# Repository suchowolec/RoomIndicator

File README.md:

# RoomIndicator
Small AVR project designed to indicate the room occupancy based on light.

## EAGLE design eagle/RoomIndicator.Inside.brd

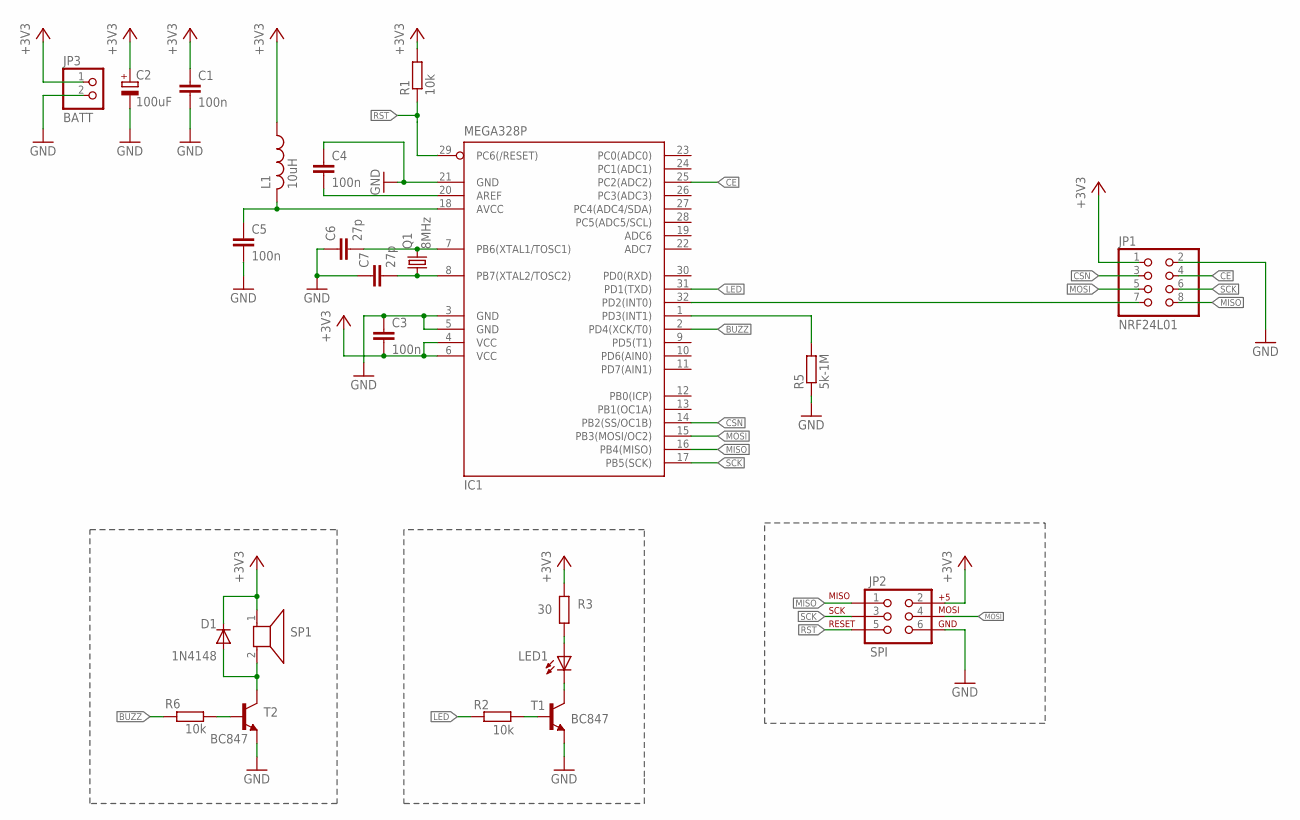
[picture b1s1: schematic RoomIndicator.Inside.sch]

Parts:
C1: 100n; C025-025X050
C2: 100uF; E2,5-5
C3, C4, C5: 100n; C0805K
C6, C7: 27p; C0805K
D1: 1N4148; DO35-7
IC1: MEGA328P; TQFP32-08
JP1: NRF24L01; 2X04
JP2: SPI; 2X3
JP3: BATT; 1X02
L1: 10uH; 0204/7
LED1: GREEN; LED5MM
Q1: 8MHz; HC49/S
R1, R2, R6: 10k; R0805
R3: 30; 0204/5
R5: 5k-1M; 0204/5
SP1: AL60PWIDE; AL80P
T1, T2: BC847; SOT23

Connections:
+3V3: C1.1, C2.+, C3.2, D1.C, IC1.4 (VCC), IC1.6 (VCC), JP1.1, JP2.2, JP3.1, L1.1, R1.2, R3.1, SP1.1
AVCC: C5.1, IC1.18 (AVCC), L1.2
BUZZ: IC1.2 (PD4(XCK/T0)), R6.1
CE: IC1.25 (PC2(ADC2)), JP1.4
CSN: IC1.14 (PB2(SS/OC1B)), JP1.3
GND: C1.2, C2.-, C3.1, C4.1, C5.2, C6.1, C7.1, IC1.3 (GND), IC1.5 (GND), IC1.21 (GND), JP1.2, JP2.6, JP3.2, R5.1, T1.2 (E), T2.2 (E)
INT0: IC1.32 (PD2(INT0)), JP1.7
INT1: IC1.1 (PD3(INT1)), R5.2
LED: IC1.31 (PD1(TXD)), R2.2
MISO: IC1.16 (PB4(MISO)), JP1.8, JP2.1
MOSI: IC1.15 (PB3(MOSI/OC2)), JP1.5, JP2.4
unnamed: C4.2, IC1.20 (AREF)
unnamed: R6.2, T2.1 (B)
unnamed: LED1.A, R3.2
unnamed: R2.1, T1.1 (B)
unnamed: LED1.K (C), T1.3 (C)
unnamed: D1.A, SP1.2, T2.3 (C)
RST: IC1.29 (PC6(/RESET)), JP2.5, R1.1
SCK: IC1.17 (PB5(SCK)), JP1.6, JP2.3
TOSC1: C6.2, IC1.7 (PB6(XTAL1/TOSC1)), Q1.2
TOSC2: C7.2, IC1.8 (PB7(XTAL2/TOSC2)), Q1.1

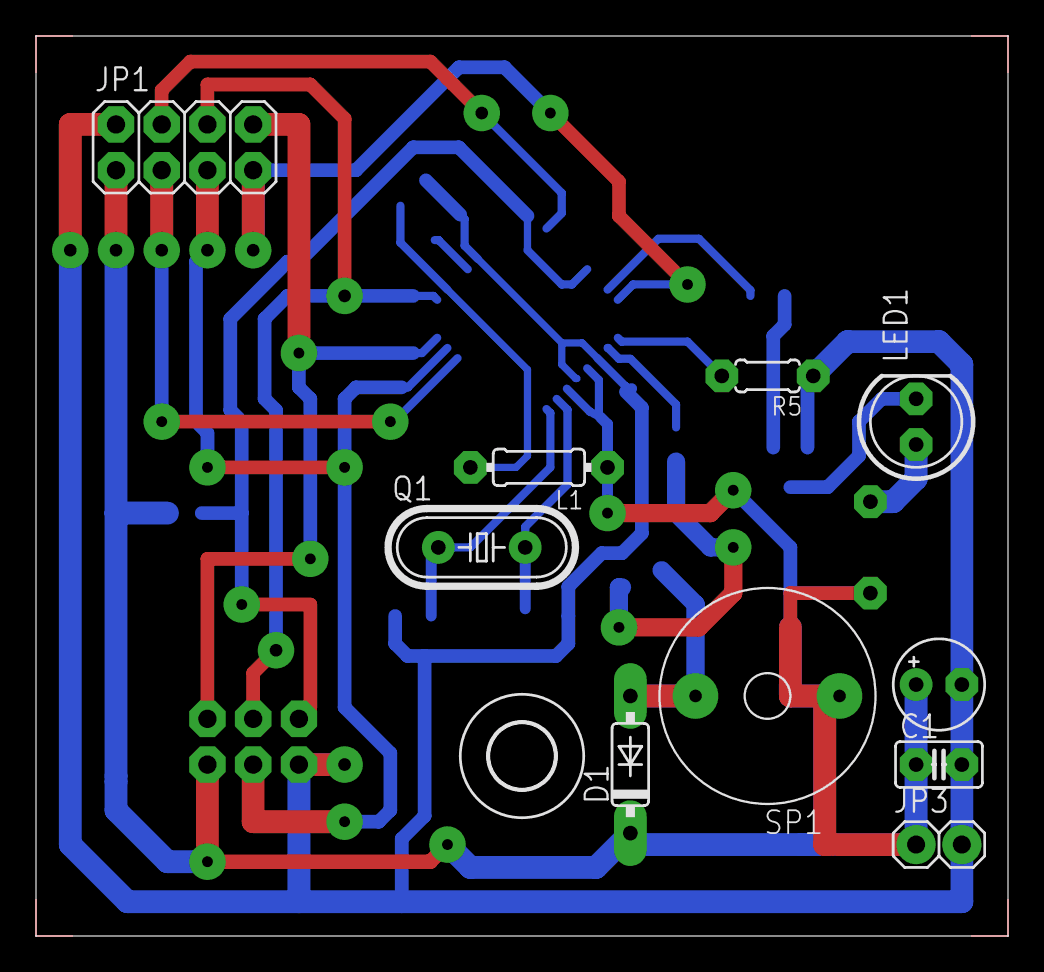
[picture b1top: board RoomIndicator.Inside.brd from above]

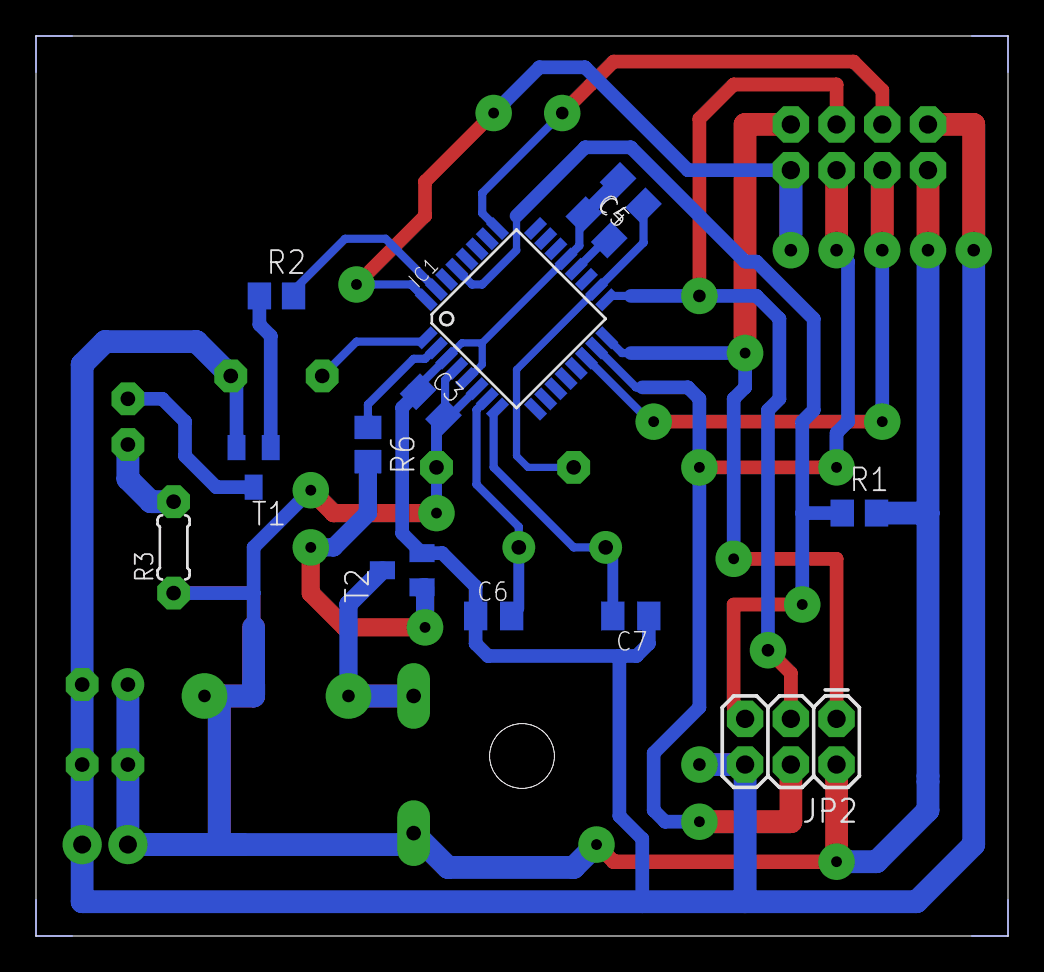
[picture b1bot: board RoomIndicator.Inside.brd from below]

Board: 2 copper layers, 54.0 x 50.0 mm, 24 parts (13 on the bottom side), 21 nets.

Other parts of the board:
U$1: 3,6

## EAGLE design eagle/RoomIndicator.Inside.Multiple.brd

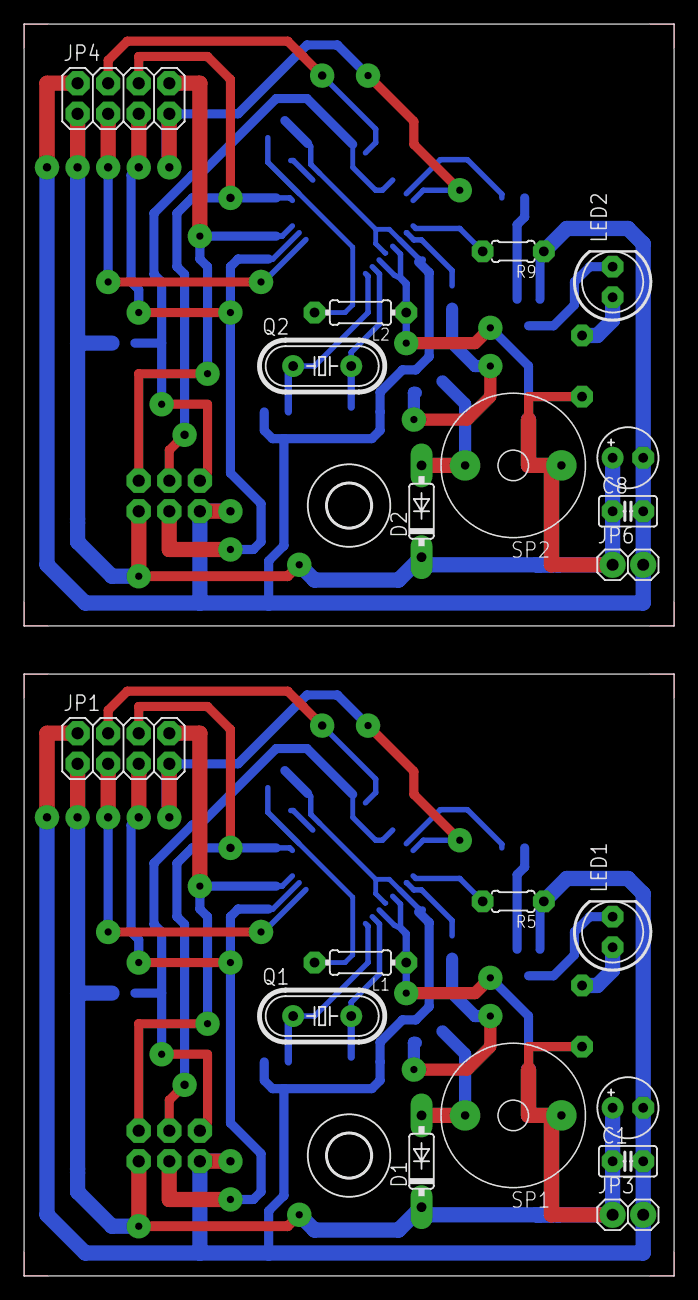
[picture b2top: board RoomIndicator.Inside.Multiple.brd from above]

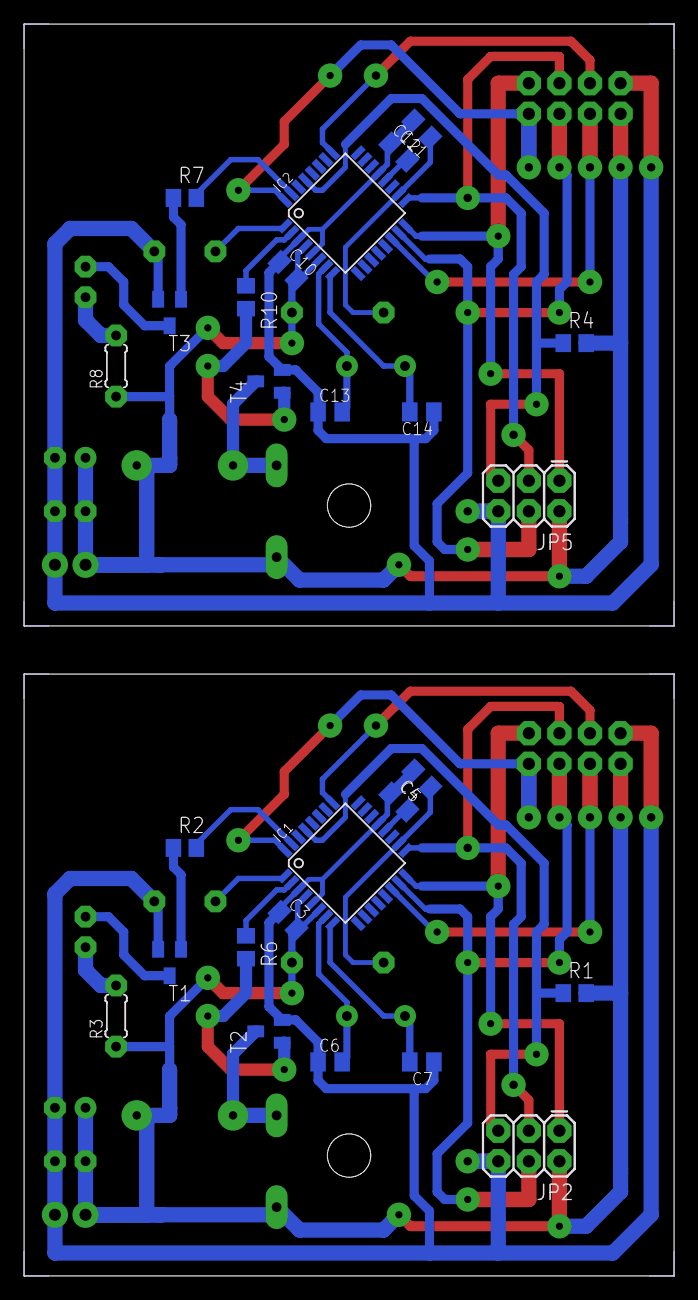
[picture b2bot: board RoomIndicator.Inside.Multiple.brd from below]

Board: 2 copper layers, 54.0 x 104.0 mm, 48 parts (26 on the bottom side), 42 nets.

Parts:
C1, C8: 100n; C025-025X050
C2, C9: 100uF; E2,5-5
C3, C4, C5, C10, C11, C12: 100n; C0805K
C6, C7, C13, C14: 27p; C0805K
D1, D2: 1N4148; DO35-7
IC1, IC2: MEGA328P; TQFP32-08
JP1, JP4: NRF24L01; 2X04
JP2, JP5: SPI; 2X3
JP3, JP6: BATT; 1X02
L1, L2: 10uH; 0204/7
LED1, LED2: GREEN; LED5MM
Q1, Q2: 8MHz; HC49/S
R1, R2, R4, R6, R7, R10: 10k; R0805
R3, R8: 30; 0204/5
R5, R9: 5k-1M; 0204/5
SP1, SP2: AL60PWIDE; AL80P
T1, T2, T3, T4: BC847; SOT23
U$1, U$2: 3,6

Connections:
+3V1: C8.1, C9.+, C10.2, D2.C, IC2.4, IC2.6, JP4.1, JP5.2, JP6.1, L2.1, R4.2, R8.1, SP2.1
+3V3: C1.1, C2.+, C3.2, D1.C, IC1.4, IC1.6, JP1.1, JP2.2, JP3.1, L1.1, R1.2, R3.1, SP1.1
AVCC: C5.1, IC1.18, L1.2
AVCC1: C12.1, IC2.18, L2.2
BUZZ: IC1.2, R6.1
BUZZ1: IC2.2, R10.1
CE: IC1.25, JP1.4
CE1: IC2.25, JP4.4
CSN: IC1.14, JP1.3
CSN1: IC2.14, JP4.3
GND: C1.2, C2.-, C3.1, C4.1, C5.2, C6.1, C7.1, IC1.3, IC1.5, IC1.21, JP1.2, JP2.6, JP3.2, R5.1, T1.2, T2.2
GND1: C8.2, C9.-, C10.1, C11.1, C12.2, C13.1, C14.1, IC2.3, IC2.5, IC2.21, JP4.2, JP5.6, JP6.2, R9.1, T3.2, T4.2
INT0: IC1.32, JP1.7
INT1: IC1.1, R5.2
INT2: IC2.1, R9.2
INT3: IC2.32, JP4.7
LED: IC1.31, R2.2
LED1: IC2.31, R7.2
MISO: IC1.16, JP1.8, JP2.1
MISO1: IC2.16, JP4.8, JP5.1
MOSI: IC1.15, JP1.5, JP2.4
MOSI1: IC2.15, JP4.5, JP5.4
unnamed: C4.2, IC1.20
unnamed: R6.2, T2.1
unnamed: LED1.A, R3.2
unnamed: R2.1, T1.1
unnamed: LED1.K, T1.3
unnamed: C11.2, IC2.20
unnamed: R7.1, T3.1
unnamed: D1.A, SP1.2, T2.3
unnamed: LED2.K, T3.3
unnamed: D2.A, SP2.2, T4.3
unnamed: R10.2, T4.1
unnamed: LED2.A, R8.2
RST: IC1.29, JP2.5, R1.1
RST1: IC2.29, JP5.5, R4.1
SCK: IC1.17, JP1.6, JP2.3
SCK1: IC2.17, JP4.6, JP5.3
TOSC1: C6.2, IC1.7, Q1.2
TOSC2: C7.2, IC1.8, Q1.1
TOSC3: C14.2, IC2.8, Q2.1
TOSC4: C13.2, IC2.7, Q2.2

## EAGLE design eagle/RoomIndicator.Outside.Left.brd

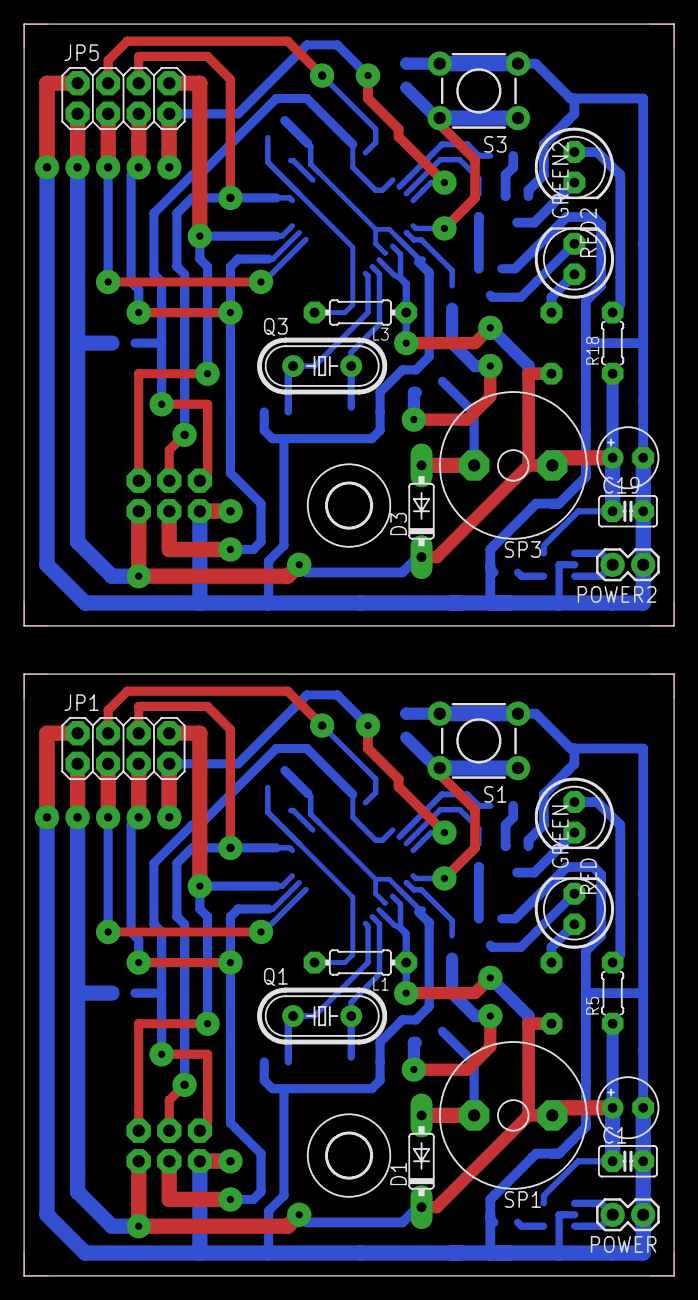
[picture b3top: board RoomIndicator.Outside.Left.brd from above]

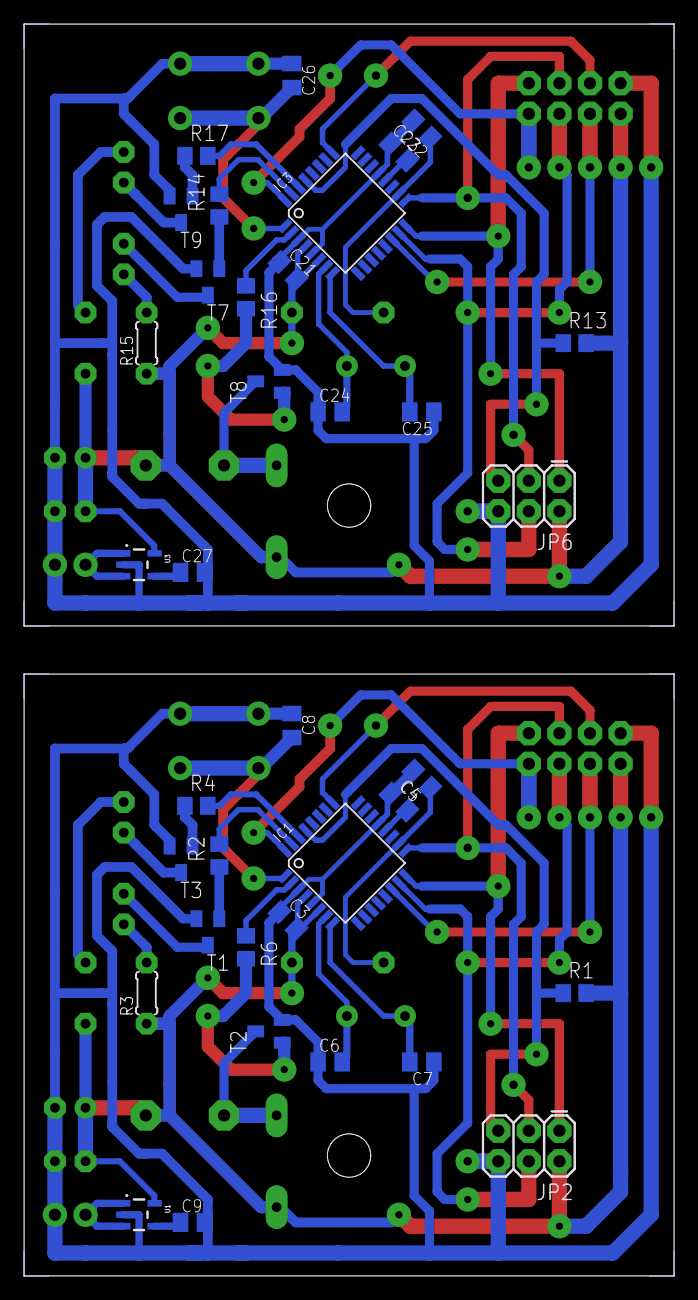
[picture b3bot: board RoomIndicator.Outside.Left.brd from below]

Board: 2 copper layers, 54.0 x 104.0 mm, 62 parts (36 on the bottom side), 54 nets.

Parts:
C1, C19: 100n; C025-025X050
C2, C20: 100uF; E2,5-5
C3, C4, C5, C8, C21, C22, C23, C26: 100n; C0805K
C6, C7, C24, C25: 27p; C0805K
C9, C27: 180p; C0805K
D1, D3: 1N4148; DO35-7
GREEN, GREEN2: GREEN; LED5MM
IC1, IC3: MEGA328P; TQFP32-08
JP1, JP5: NRF24L01; 2X04
JP2, JP6: SPI; 2X3
L1, L3: 10uH; 0204/7
POWER, POWER2: 1X02
Q1, Q3: 8MHz; HC49/S
R1, R2, R4, R6, R13, R14, R16, R17: 10k; R0805
R3, R5, R15, R18: 30; 0204/5
RED, RED2: GREEN; LED5MM
S1, S3: TACTILE-PTH
SP1, SP3: AL60P
T1, T2, T3, T7, T8, T9: BC847; SOT23
U1, U3: 3.3V/150mA; SOT23-5
U$1, U$3: 3,6

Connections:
+3V2: C19.1, C20.+, C21.2, D3.C, IC3.4, IC3.6, JP5.1, JP6.2, L3.1, R13.2, R15.1, R18.1, SP3.1, U3.5
+3V3: C1.1, C2.+, C3.2, D1.C, IC1.4, IC1.6, JP1.1, JP2.2, L1.1, R1.2, R3.1, R5.1, SP1.1, U1.5
AVCC: C5.1, IC1.18, L1.2
AVCC2: C23.1, IC3.18, L3.2
BLUE: IC1.31, R2.2
BLUE2: IC3.31, R14.2
BUZZ: IC1.2, R6.1
BUZZ2: IC3.2, R16.1
CE: IC1.25, JP1.4
CE2: IC3.25, JP5.4
CSN: IC1.14, JP1.3
CSN2: IC3.14, JP5.3
GND: C1.2, C2.-, C3.1, C4.1, C5.2, C6.1, C7.1, C8.1, C9.2, IC1.3, IC1.5, IC1.21, JP1.2, JP2.6, POWER.1, S1.3, S1.4, T1.2, T2.2, T3.2, U1.2
GND2: C19.2, C20.-, C21.1, C22.1, C23.2, C24.1, C25.1, C26.1, C27.2, IC3.3, IC3.5, IC3.21, JP5.2, JP6.6, POWER2.1, S3.3, S3.4, T7.2, T8.2, T9.2, U3.2
INT0: IC1.32, JP1.7
INT1: C8.2, IC1.1, S1.1, S1.2
INT4: C26.2, IC3.1, S3.1, S3.2
INT5: IC3.32, JP5.7
MISO: IC1.16, JP1.8, JP2.1
MISO2: IC3.16, JP5.8, JP6.1
MOSI: IC1.15, JP1.5, JP2.4
MOSI2: IC3.15, JP5.5, JP6.4
unnamed: POWER.2, U1.1, U1.3
unnamed: R4.1, T3.1
unnamed: RED.K, T3.3
unnamed: C4.2, IC1.20
unnamed: R6.2, T2.1
unnamed: GREEN.A, R3.2
unnamed: R5.2, RED.A
unnamed: C9.1, U1.4
unnamed: R2.1, T1.1
unnamed: GREEN.K, T1.3
unnamed: D1.A, SP1.2, T2.3
unnamed: C22.2, IC3.20
unnamed: R14.1, T7.1
unnamed: GREEN2.K, T7.3
unnamed: D3.A, SP3.2, T8.3
unnamed: R16.2, T8.1
unnamed: GREEN2.A, R15.2
unnamed: POWER2.2, U3.1, U3.3
unnamed: R17.1, T9.1
unnamed: RED2.K, T9.3
unnamed: R18.2, RED2.A
unnamed: C27.1, U3.4
RED: IC1.30, R4.2
RED2: IC3.30, R17.2
RST: IC1.29, JP2.5, R1.1
RST2: IC3.29, JP6.5, R13.1
SCK: IC1.17, JP1.6, JP2.3
SCK2: IC3.17, JP5.6, JP6.3
TOSC1: C6.2, IC1.7, Q1.2
TOSC2: C7.2, IC1.8, Q1.1
TOSC5: C25.2, IC3.8, Q3.1
TOSC6: C24.2, IC3.7, Q3.2

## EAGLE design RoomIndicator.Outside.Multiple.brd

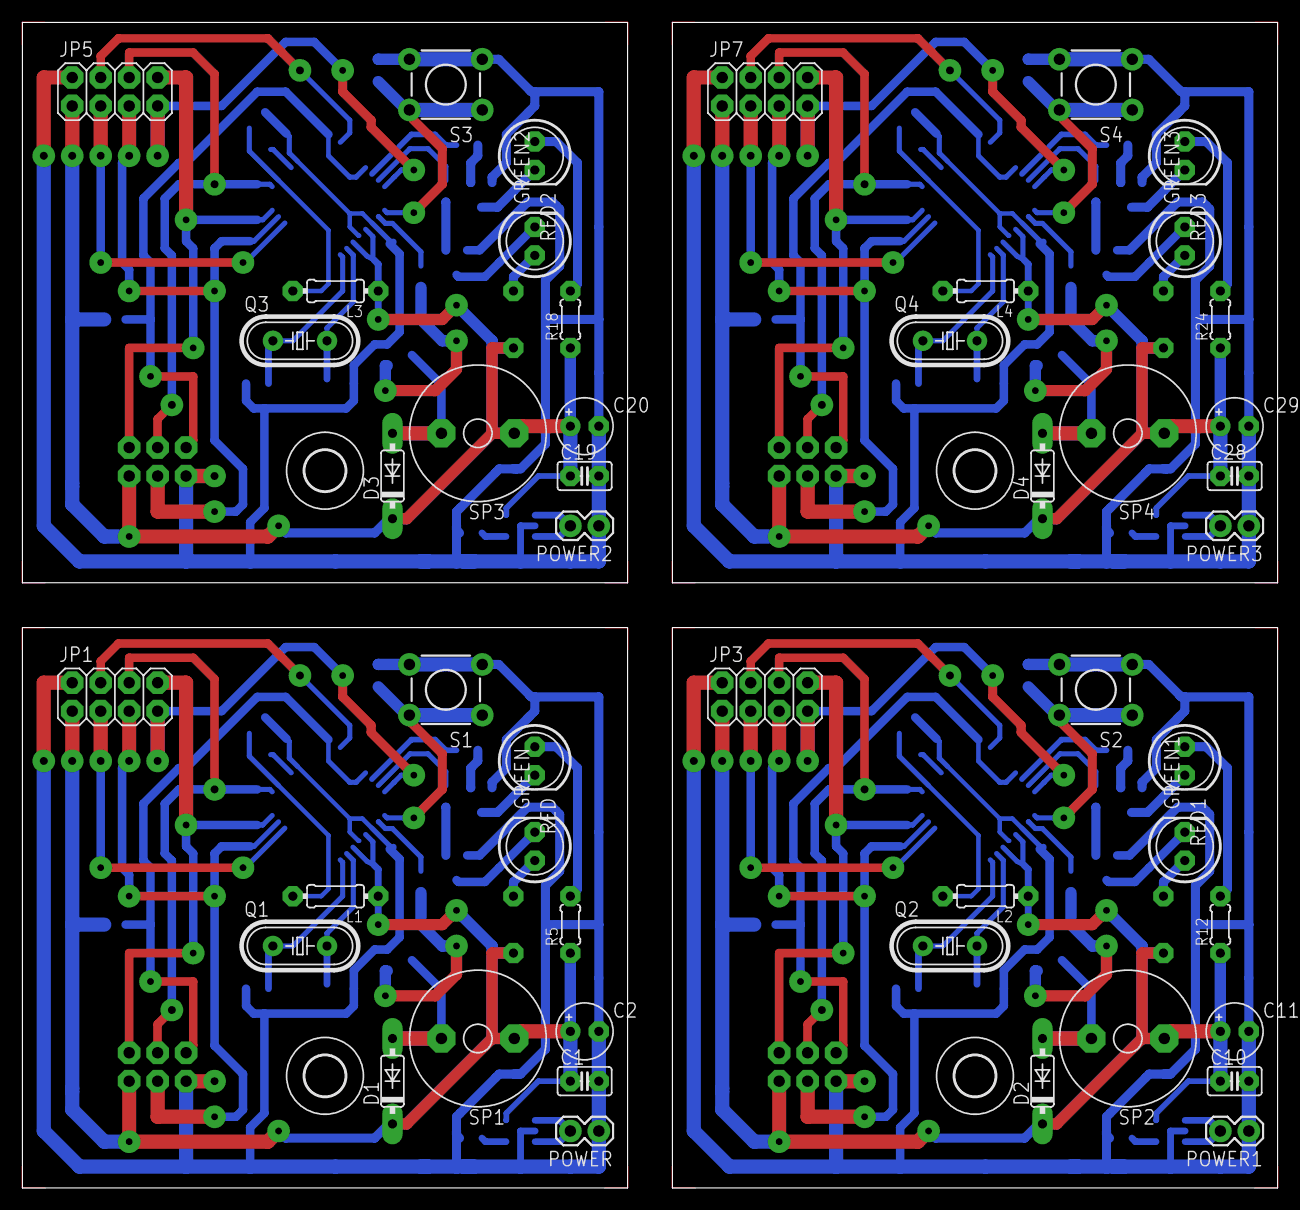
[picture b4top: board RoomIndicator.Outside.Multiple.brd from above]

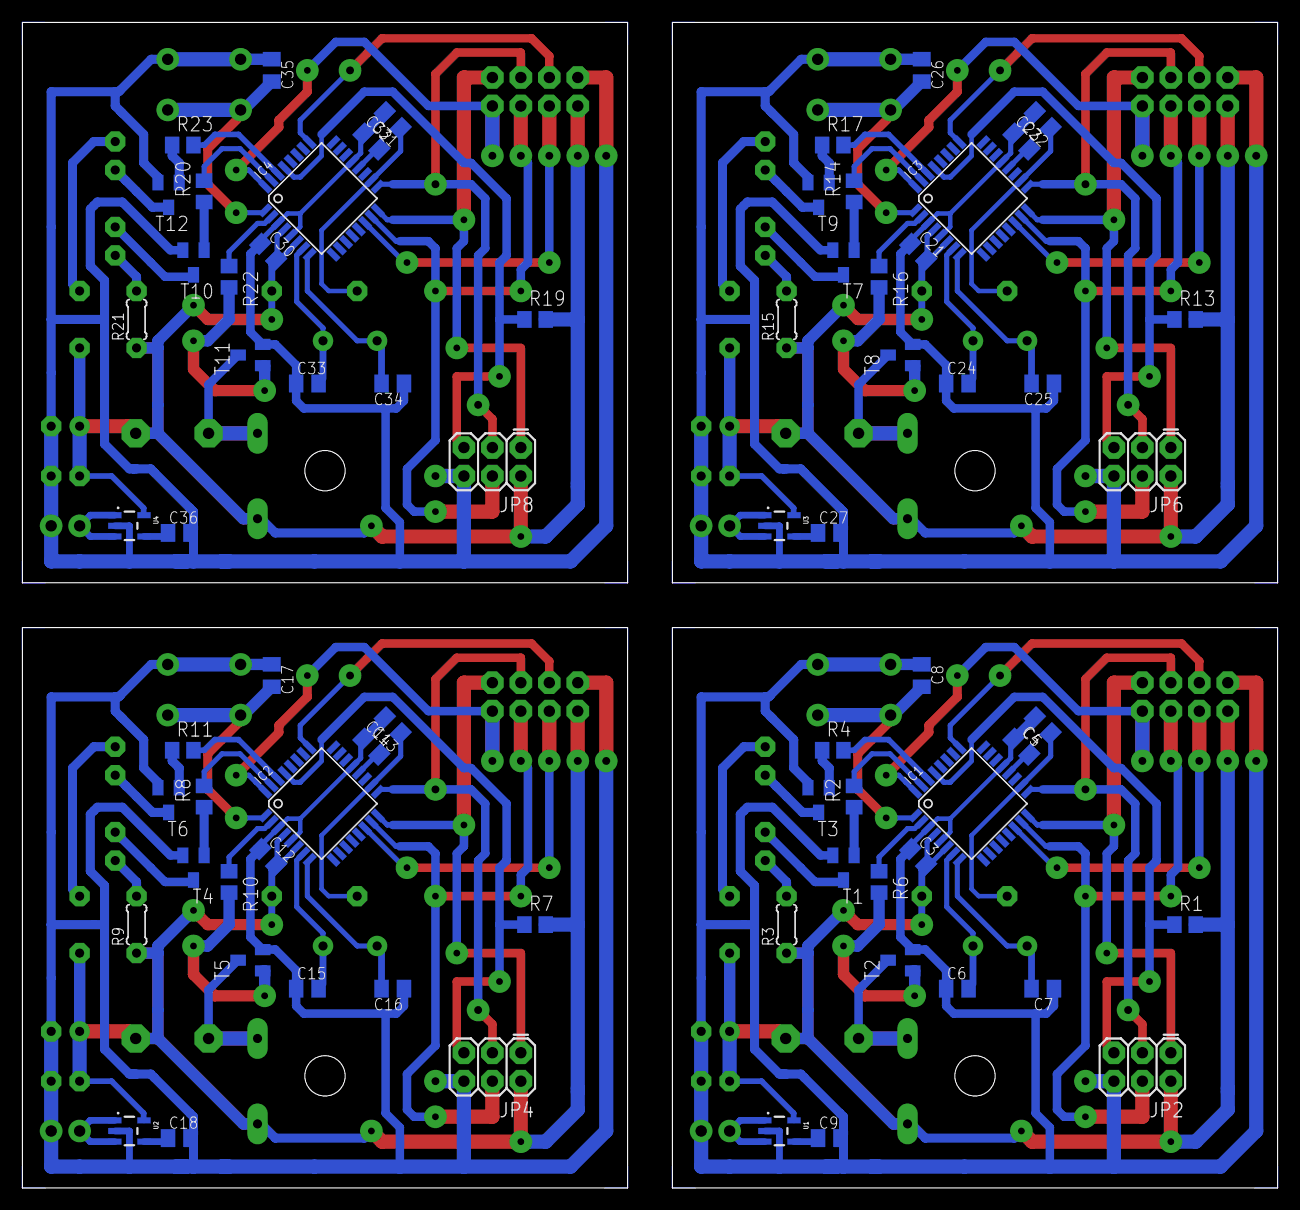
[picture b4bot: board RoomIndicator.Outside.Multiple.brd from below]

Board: 2 copper layers, 112.0 x 104.0 mm, 124 parts (72 on the bottom side), 108 nets.

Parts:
C1, C10, C19, C28: 100n; C025-025X050
C2, C11, C20, C29: 100uF; E2,5-5
C3, C4, C5, C8, C12, C13, C14, C17, C21, C22, C23, C26, C30, C31, C32, C35: 100n; C0805K
C6, C7, C15, C16, C24, C25, C33, C34: 27p; C0805K
C9, C18, C27, C36: 180p; C0805K
D1, D2, D3, D4: 1N4148; DO35-7
GREEN, GREEN1, GREEN2, GREEN3: GREEN; LED5MM
IC1, IC2, IC3, IC4: MEGA328P; TQFP32-08
JP1, JP3, JP5, JP7: NRF24L01; 2X04
JP2, JP4, JP6, JP8: SPI; 2X3
L1, L2, L3, L4: 10uH; 0204/7
POWER, POWER1, POWER2, POWER3: 1X02
Q1, Q2, Q3, Q4: 8MHz; HC49/S
R1, R2, R4, R6, R7, R8, R10, R11, R13, R14, R16, R17, R19, R20, R22, R23: 10k; R0805
R3, R5, R9, R12, R15, R18, R21, R24: 30; 0204/5
RED, RED1, RED2, RED3: GREEN; LED5MM
S1, S2, S3, S4: TACTILE-PTH
SP1, SP2, SP3, SP4: AL60P
T1, T2, T3, T4, T5, T6, T7, T8, T9, T10, T11, T12: BC847; SOT23
U1, U2, U3, U4: 3.3V/150mA; SOT23-5
U$1, U$2, U$3, U$4: 3,6

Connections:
+3V1: C10.1, C11.+, C12.2, D2.C, IC2.4, IC2.6, JP3.1, JP4.2, L2.1, R7.2, R9.1, R12.1, SP2.1, U2.5
+3V2: C19.1, C20.+, C21.2, D3.C, IC3.4, IC3.6, JP5.1, JP6.2, L3.1, R13.2, R15.1, R18.1, SP3.1, U3.5
+3V3: C1.1, C2.+, C3.2, D1.C, IC1.4, IC1.6, JP1.1, JP2.2, L1.1, R1.2, R3.1, R5.1, SP1.1, U1.5
+3V4: C28.1, C29.+, C30.2, D4.C, IC4.4, IC4.6, JP7.1, JP8.2, L4.1, R19.2, R21.1, R24.1, SP4.1, U4.5
AVCC: C5.1, IC1.18, L1.2
AVCC1: C14.1, IC2.18, L2.2
AVCC2: C23.1, IC3.18, L3.2
AVCC3: C32.1, IC4.18, L4.2
BLUE: IC1.31, R2.2
BLUE1: IC2.31, R8.2
BLUE2: IC3.31, R14.2
BLUE3: IC4.31, R20.2
BUZZ: IC1.2, R6.1
BUZZ1: IC2.2, R10.1
BUZZ2: IC3.2, R16.1
BUZZ3: IC4.2, R22.1
CE: IC1.25, JP1.4
CE1: IC2.25, JP3.4
CE2: IC3.25, JP5.4
CE3: IC4.25, JP7.4
CSN: IC1.14, JP1.3
CSN1: IC2.14, JP3.3
CSN2: IC3.14, JP5.3
CSN3: IC4.14, JP7.3
GND: C1.2, C2.-, C3.1, C4.1, C5.2, C6.1, C7.1, C8.1, C9.2, IC1.3, IC1.5, IC1.21, JP1.2, JP2.6, POWER.1, S1.3, S1.4, T1.2, T2.2, T3.2, U1.2
GND1: C10.2, C11.-, C12.1, C13.1, C14.2, C15.1, C16.1, C17.1, C18.2, IC2.3, IC2.5, IC2.21, JP3.2, JP4.6, POWER1.1, S2.3, S2.4, T4.2, T5.2, T6.2, U2.2
GND2: C19.2, C20.-, C21.1, C22.1, C23.2, C24.1, C25.1, C26.1, C27.2, IC3.3, IC3.5, IC3.21, JP5.2, JP6.6, POWER2.1, S3.3, S3.4, T7.2, T8.2, T9.2, U3.2
GND3: C28.2, C29.-, C30.1, C31.1, C32.2, C33.1, C34.1, C35.1, C36.2, IC4.3, IC4.5, IC4.21, JP7.2, JP8.6, POWER3.1, S4.3, S4.4, T10.2, T11.2, T12.2, U4.2
INT0: IC1.32, JP1.7
INT1: C8.2, IC1.1, S1.1, S1.2
INT2: C17.2, IC2.1, S2.1, S2.2
INT3: IC2.32, JP3.7
INT4: C26.2, IC3.1, S3.1, S3.2
INT5: IC3.32, JP5.7
INT6: C35.2, IC4.1, S4.1, S4.2
INT7: IC4.32, JP7.7
MISO: IC1.16, JP1.8, JP2.1
MISO1: IC2.16, JP3.8, JP4.1
MISO2: IC3.16, JP5.8, JP6.1
MISO3: IC4.16, JP7.8, JP8.1
MOSI: IC1.15, JP1.5, JP2.4
MOSI1: IC2.15, JP3.5, JP4.4
MOSI2: IC3.15, JP5.5, JP6.4
MOSI3: IC4.15, JP7.5, JP8.4
unnamed: POWER.2, U1.1, U1.3
unnamed: R4.1, T3.1
unnamed: RED.K, T3.3
unnamed: C4.2, IC1.20
unnamed: R6.2, T2.1
unnamed: GREEN.A, R3.2
unnamed: R5.2, RED.A
unnamed: C9.1, U1.4
unnamed: R2.1, T1.1
unnamed: GREEN.K, T1.3
unnamed: D1.A, SP1.2, T2.3
unnamed: C13.2, IC2.20
unnamed: R8.1, T4.1
unnamed: GREEN1.K, T4.3
unnamed: D2.A, SP2.2, T5.3
unnamed: R10.2, T5.1
unnamed: GREEN1.A, R9.2
unnamed: POWER1.2, U2.1, U2.3
unnamed: R11.1, T6.1
unnamed: RED1.K, T6.3
unnamed: R12.2, RED1.A
unnamed: C18.1, U2.4
unnamed: C22.2, IC3.20
unnamed: R14.1, T7.1
unnamed: GREEN2.K, T7.3
unnamed: D3.A, SP3.2, T8.3
unnamed: R16.2, T8.1
unnamed: GREEN2.A, R15.2
unnamed: POWER2.2, U3.1, U3.3
unnamed: R17.1, T9.1
unnamed: RED2.K, T9.3
unnamed: R18.2, RED2.A
unnamed: C27.1, U3.4
unnamed: C31.2, IC4.20
unnamed: R20.1, T10.1
unnamed: GREEN3.K, T10.3
unnamed: D4.A, SP4.2, T11.3
unnamed: R22.2, T11.1
unnamed: GREEN3.A, R21.2
unnamed: POWER3.2, U4.1, U4.3
unnamed: R23.1, T12.1
unnamed: RED3.K, T12.3
unnamed: R24.2, RED3.A
unnamed: C36.1, U4.4
RED: IC1.30, R4.2
RED1: IC2.30, R11.2
RED2: IC3.30, R17.2
RED3: IC4.30, R23.2
RST: IC1.29, JP2.5, R1.1
RST1: IC2.29, JP4.5, R7.1
RST2: IC3.29, JP6.5, R13.1
RST3: IC4.29, JP8.5, R19.1
SCK: IC1.17, JP1.6, JP2.3
SCK1: IC2.17, JP3.6, JP4.3
SCK2: IC3.17, JP5.6, JP6.3
SCK3: IC4.17, JP7.6, JP8.3
TOSC1: C6.2, IC1.7, Q1.2
TOSC2: C7.2, IC1.8, Q1.1
TOSC3: C16.2, IC2.8, Q2.1
TOSC4: C15.2, IC2.7, Q2.2
TOSC5: C25.2, IC3.8, Q3.1
TOSC6: C24.2, IC3.7, Q3.2
TOSC7: C34.2, IC4.8, Q4.1
TOSC8: C33.2, IC4.7, Q4.2

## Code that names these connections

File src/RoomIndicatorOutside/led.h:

/*
 * led.h
 *
 *  Created on: 16-08-2015
 *      Author: Czarek
 */

#ifndef LED_H_
#define LED_H_

#include <avr/io.h>

#define PORT_LED    	PORTD
#define PORT_BUZZ   	PORTD
#define LED_RED   		PD0
#define LED_GREEN 		PD1
#define BUZZ 			PD4
#define BTN				PD3
#define IRQ				PD2

#define LED_RED_ON 		PORT_LED |= _BV(LED_RED)
#define LED_RED_OFF 	PORT_LED &= ~(_BV(LED_RED))
#define LED_GREEN_ON 	PORT_LED |= _BV(LED_GREEN)
#define LED_GREEN_OFF	PORT_LED &= ~(_BV(LED_GREEN))
#define BUZZ_ON 		PORT_BUZZ |= _BV(BUZZ);
#define BUZZ_OFF		PORT_BUZZ &= ~(_BV(BUZZ));

extern void blink_red_led(uint8_t blinks);
extern void blink_green_led(uint8_t blinks);
extern void beep(uint8_t beeps);

#endif /* LED_H_ */

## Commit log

2015-07-21 Eagle schemas and boards
2015-07-21 Eagle project files
2015-07-21 Moving eagle files to separated directory
2015-07-24 Replacing buzzer package
2015-07-24 Boards for printing
2015-08-07 Adding element places
2015-08-27 Source code
2015-08-27 Circuit diagrams

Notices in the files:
parts and their libraries:
SparkFun-Connectors: Licensing: Creative Commons ShareAlike 4.0 International - https://creativecommons.org/licenses/by-sa/4.0
